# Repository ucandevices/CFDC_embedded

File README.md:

# USB CAN FD Converter (CFUC)

> **Open source USB ↔ CAN FD bridge. ISO CAN FD and classic CAN to USB virtual COM port — no proprietary drivers on Windows, Linux or macOS. Python-can plugin included.**

The **CAN FD USB Converter (CFUC)** is a small open-source USB dongle built around an **STM32G431** (CAN FD-capable MCU) and an **MCP2542FD** transceiver. It exposes both classic CAN (up to 1 Mbit/s) and **ISO CAN FD** (data phase up to 5 Mbit/s) to a PC over a USB CDC virtual COM port, and ships with a **python-can plugin** so it slots into existing CAN tooling out of the box.

This repo is the **embedded firmware and hardware**. For the host-side python-can plugin and example scripts see [`tools/`](tools/).

A commercial CAN FD adapter typically costs hundreds of euros. This one is around **$22** on Tindie.

---

## Features

- **ISO CAN FD** and classic CAN (selectable per channel)
- Arbitration phase up to **1 Mbit/s**, data phase up to **5 Mbit/s**
- USB CDC Virtual COM Port — no driver on Linux / macOS / Windows 10+
- **python-can plugin** included under [`tools/`](tools/)
- Two CAN FD firmware flavors:
  - Native uCAN firmware (this repo, `firmware/`)
  - **gs_usb / budgetcan** compatible firmware under [`gsusb_firmware/budgetcan_fw/`](gsusb_firmware/budgetcan_fw/) — enumerates as a standard `gs_usb` device on Linux (works directly with SocketCAN's `gs_usb` kernel driver)
- USB DFU bootloader for in-field firmware updates
- Open hardware (KiCad sources under `pcb/`)

---

## Where to buy

| Where | Region | Link |
|---|---|---|
| **Tindie** | Worldwide | https://www.tindie.com/stores/lll7/ |
| **Lectronz** | EU | https://lectronz.com/stores/ucandevices |
| **Elty** | Poland / EU | https://elty.pl/ |
| **Kamami** | Poland / EU | https://kamami.pl/ |

---

## Quickstart

### gs_usb firmware (recommended on Linux)

Flash the `gsusb_firmware/budgetcan_fw/` build and the device appears as a native SocketCAN interface:

```bash
sudo ip link set can0 up type can bitrate 500000 dbitrate 2000000 fd on
candump can0
```

### Native firmware (python-can)

```python
import can
bus = can.Bus(interface='cfuc', channel='/dev/ttyACM0', bitrate=500000)
for msg in bus:
    print(msg)
```

The python-can plugin lives in [`tools/`](tools/) along with example scripts.

---

## Repository layout

| Directory | Contents |
|---|---|
| [`firmware/`](firmware/) | Native CFUC firmware for STM32G431 (CubeMX project `CDC_libUSB_basic.ioc`, Makefile build). |
| [`gsusb_firmware/budgetcan_fw/`](gsusb_firmware/budgetcan_fw/) | Alternative gs_usb / [budgetcan](https://github.com/budgetcan/budgetcan_fw) firmware — enumerates as a standard `gs_usb` device on Linux. |
| [`pcb/`](pcb/) | Open hardware KiCad project for the CFUC board. |
| [`tools/`](tools/) | python-can plugin, host-side helpers, examples and the `uCAN_CAN_Viewer` GUI. |
| [`doc/`](doc/) | Datasheets for the STM32G431, MCP2542FD transceiver, USB ESD protection. |

For per-folder detail see:
- [`pcb/README.md`](pcb/README.md) — hardware
- [`firmware/README.md`](firmware/README.md) — embedded firmware
- [`tools/README.md`](tools/README.md) — host tools and python-can plugin

---

## Build (native firmware)

The firmware is built with arm-none-eabi-gcc and a hand-written Makefile:

```bash
cd firmware
make -j4
```

Output: `firmware/build/CDC_libUSB_basic.elf`.

## Flash

### SWD (ST-Link)

```bash
STM32_Programmer_CLI -c port=SWD freq=4000 -w firmware/build/CDC_libUSB_basic.elf -v -hardRst
```

### USB DFU

Trigger DFU from a running device (send `boot\r` over the virtual COM port), then:

```bash
STM32_Programmer_CLI -c port=USB1 -w firmware/build/CDC_libUSB_basic.elf -v -hardRst
```

See [`tools/CFUC_Upload.sh`](tools/CFUC_Upload.sh) for a one-shot flashing script.

---

## FAQ

**What is the cheapest open source USB CAN FD adapter?**
The uCanDevices CAN FD USB Converter (CFUC) is around $22 and is fully open source — STM32G431 firmware in this repo, KiCad hardware sources in `pcb/`, python-can plugin in `tools/`. Commercial CAN FD adapters typically start at several hundred euros.

**Does it support ISO CAN FD or only non-ISO?**
ISO CAN FD. The MCP2542FD transceiver and the STM32G431's FDCAN peripheral both support the ISO CAN FD specification (the one used in current automotive ECUs).

**Does it work with python-can?**
Yes — a python-can plugin is included under [`tools/`](tools/). The device is also available as a `gs_usb` device using the alternate firmware under [`gsusb_firmware/`](gsusb_firmware/), which is supported by python-can's built-in `gs_usb` interface and by Linux SocketCAN directly.

**Can it work with Linux SocketCAN natively?**
Yes — flash the gs_usb firmware from [`gsusb_firmware/budgetcan_fw/`](gsusb_firmware/budgetcan_fw/). The device then enumerates as a `can0` SocketCAN interface and works with `candump`, `cansend`, `cangw` and other can-utils, as well as anything that talks SocketCAN.

**What bit rates are supported?**
Up to 1 Mbit/s arbitration phase, up to 5 Mbit/s data phase (CAN FD bit rate switching). Classic CAN frames are also supported on the same channel.

**Is a driver required?**
No driver on Linux or macOS. On Windows 10+ the device enumerates as a virtual COM port using the built-in CDC class driver.

---

## Related projects

- gs_usb / budgetcan firmware: https://github.com/budgetcan/budgetcan_fw
- Sibling products: [USB CAN Converter (UCCB)](https://ucandevices.github.io/uccb.html), [USB LIN Converter](https://ucandevices.github.io/ulc.html), [SENT (J2716) USB Converter](https://ucandevices.github.io/sentusb.html)

## Links

- Product page: https://ucandevices.github.io/cfuc.html
- All uCanDevices products: https://ucandevices.github.io/
- Contact: devices.ucan@gmail.com

## License

See [LICENSE](LICENSE).

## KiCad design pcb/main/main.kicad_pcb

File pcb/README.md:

# PCB board

To open schematic and PCB use KiCad 5.1.4 or higher.

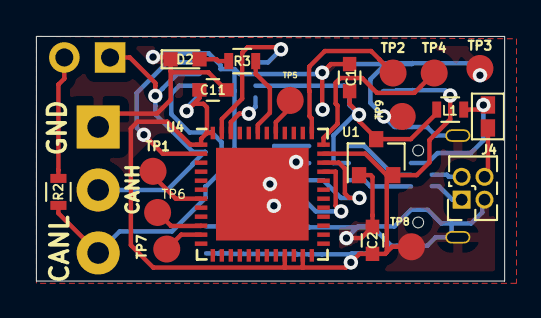
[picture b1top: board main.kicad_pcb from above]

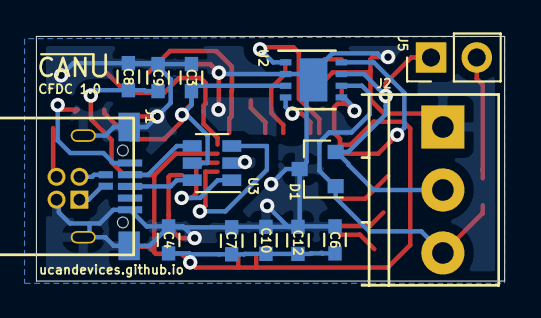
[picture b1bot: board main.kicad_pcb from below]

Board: 2 copper layers, 26.0 x 13.6 mm, 36 parts (16 on the bottom side), 25 nets.

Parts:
C1, C4, C10: 1u; C_0603
C2, C3, C6, C9, C11: 100n; C_0603
C7, C8: 10u; C_0603
C12: 4,7u; C_0603
D1: PESD2CAN; SOT-23
D2: LED; LED_0603
J1: USBMCS1B5W
J2: Screw_Terminal_01x03/3,5; TerminalBlock_Phoenix_PT-3.5mm_3pol
J4: Conn_01x04_Male; Pin_Header_Straight_2x02_Pitch1.27mm
J5: Conn_01x02_Female; Pin_Header_Straight_1x02_Pitch2.54mm
JP1, JP2: SolderJumper_2_Open; mini_GS2
JP3: SolderJumper_2_Open; GS2
L1: BLM18TG601TN1D; R_0603
R2: 120; R_0603
R3: 1k; R_0603
TP1, TP2, TP3, TP4, TP5, TP6, TP7, TP8, TP9: TestPoint; Measurement_Point_Round-SMD-Pad_Small
U1: MCP1700-3302E_SOT23; SOT-23
U2: MCP2542FDxMF; DFN-8-1EP_3x3mm_Pitch0.65mm
U3: USBLC6-2SC6; SOT-23-6
U4: STM32G431CBUx; QFN-48-1EP_7x7mm_Pitch0.5mm

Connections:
+3V3: C2.2, C4.1, C6.2, C7.2, C8.1, C9.2, C10.2, C11.2, C12.2, TP8.1, U1.2, U2.5, U4.1, U4.21, U4.23, U4.35, U4.48
+5V: C1.1, C3.1, L1.2, U1.3, U2.3, U3.5
/CANH: D1.2, J2.2, J5.1, U2.7
/CANL: D1.1, J2.3, R2.1, U2.6
CAN_RX: U2.4, U4.46
CAN_STBY: U2.8, U4.2
CAN_TX: U2.1, U4.47
D+: J1.3, U3.6
D-: J1.2, U3.4
GND: C1.2, C2.1, C3.2, C4.2, C6.1, C7.1, C8.2, C9.1, C10.1, C11.1, C12.1, D1.3, D2.1, J1.5, J1.6, J2.1, J4.3, TP3.1, TP9.1, U1.1, U2.2, U2.9, U3.2, U4.49
unnamed: D2.2, R3.2
unnamed: J4.1, JP1.1
unnamed: J4.2, JP2.1
unnamed: J4.4, JP3.1
unnamed: J5.2, R2.2
unnamed: R3.1, U4.43
unnamed: TP6.1, U4.10
unnamed: TP7.1, U4.11
RESET: TP1.1, U4.7
SW_CLK: TP2.1, U4.37
SW_DIO: TP4.1, U4.36
SW_SWO: TP5.1, U4.41
USB_DM: U3.3, U4.33
USB_DP: U3.1, U4.34
VB_N: J1.1, JP3.2, L1.1

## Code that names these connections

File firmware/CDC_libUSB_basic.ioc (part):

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Mcu.Name=STM32G431C(6-8-B)Ux
Mcu.Package=UFQFPN48
Mcu.UserName=STM32G431CBUx
PA11.Mode=Device
PA11.Signal=USB_DM
PA12.Mode=Device
PA12.Signal=USB_DP
PB5.GPIOParameters=GPIO_Label
PB5.GPIO_Label=LED
PB5.Signal=GPIO_Output
PB8-BOOT0.Mode=FDCANFD
PB8-BOOT0.Signal=FDCAN1_RX
PB9.Mode=FDCANFD
PB9.Signal=FDCAN1_TX
PC13.GPIOParameters=GPIO_Label
PC13.GPIO_Label=CAN_STBY
PC13.Signal=GPIO_Output
PF0-OSC_IN.Mode=HSE-External-Clock-Source
PF0-OSC_IN.Signal=RCC_OSC_IN
RCC.HSE_VALUE=8000000
RCC.SYSCLKFreq_VALUE=144000000
RCC.SYSCLKSource=RCC_SYSCLKSOURCE_PLLCLK
board=custom

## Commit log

2020-05-27 Init
2020-05-27 gitignore - debug files *.d, *.o, *.su, *.mk
2020-05-27 CDC libUSB echo
2020-05-27 Text update
2020-06-02 Toogle LED when USB data getted.
2020-06-02 FD CAN clock set to 144MHz
2020-06-07 ring module prepared
2020-06-25 jump to boot
2020-06-26 usbd_cdc.h usbd_cdc.c changed
2020-07-11 Buffer fix, init fix, change PID/VID
2020-07-14 CAN baudrate set to 100 kb/s
2020-08-04 Extended ring buffer size, add dumy tx
2020-08-06 working TX/RX with big data + delay for non thread app
2020-08-07 Padding update
2020-08-08 Add rx/tx CAN modified ring
2020-08-11 Uddate init frame siwtch
2020-08-13 Fixed packet size, add USB multipacket state machine
2020-08-14 CAN INIT + CAN TX fix
2020-08-17 CAN 1000 loop
2020-10-02 Fix usb 256 buffer reception
2020-10-05 Add status request
2020-10-14 Add go to boot
2020-10-28 Working 100 kbps clasic
2020-11-03 Add working boot, use script only !
2020-12-28 update log + boot
2021-01-08 Add reset on no status, fix boot
2021-01-18 Fix short frames reception
2021-01-23 Fix short frames workaournd delay
2021-02-20 Add wdg, fix USB sending sequence
2021-02-26 Fix low baudate
2021-12-10 switch to VCOM drivers
2021-12-30 refactor
2022-01-04 Update to new version of drivers
2022-01-04 transition to makefile
2022-01-04 Revert "Merge branch 'master' into USB_Serial"
    This reverts commit d96e453649ef5e234cbcf5469f73a4df5a9e80b5, reversing
    changes made to c05897fbabb2d481dd80c64f6f3549d51f4bff81.
2022-01-04 cleanup
2022-01-12 working
2022-03-04 bootloader fix
2022-04-08 stable version 1.0
2022-07-05 cleanup & makefile fix
2022-07-28 Add python exmaples
2022-07-29 Add ReadMe
2022-07-30 add python-gui draft
2022-08-13 Add configuraiton handling
2022-08-27 Add gui for CAN send
2022-09-02 Update messaging
2022-09-23 Add can tramission parsing
2022-09-23 Add RX and TX with CAN
2022-10-15 Release 1.0
2022-11-26 Add config eddition button
2022-11-26 Add delta view
2023-04-12 Add gsusb firmware
2023-05-08 Fix IT priories
2023-07-19 Change from serial to GS_USB
2023-07-24 Add uCANViewer with GS_USB support
2024-05-01 Add SLCAN driver
2024-05-02 Add support for SLCAN to CFUC
